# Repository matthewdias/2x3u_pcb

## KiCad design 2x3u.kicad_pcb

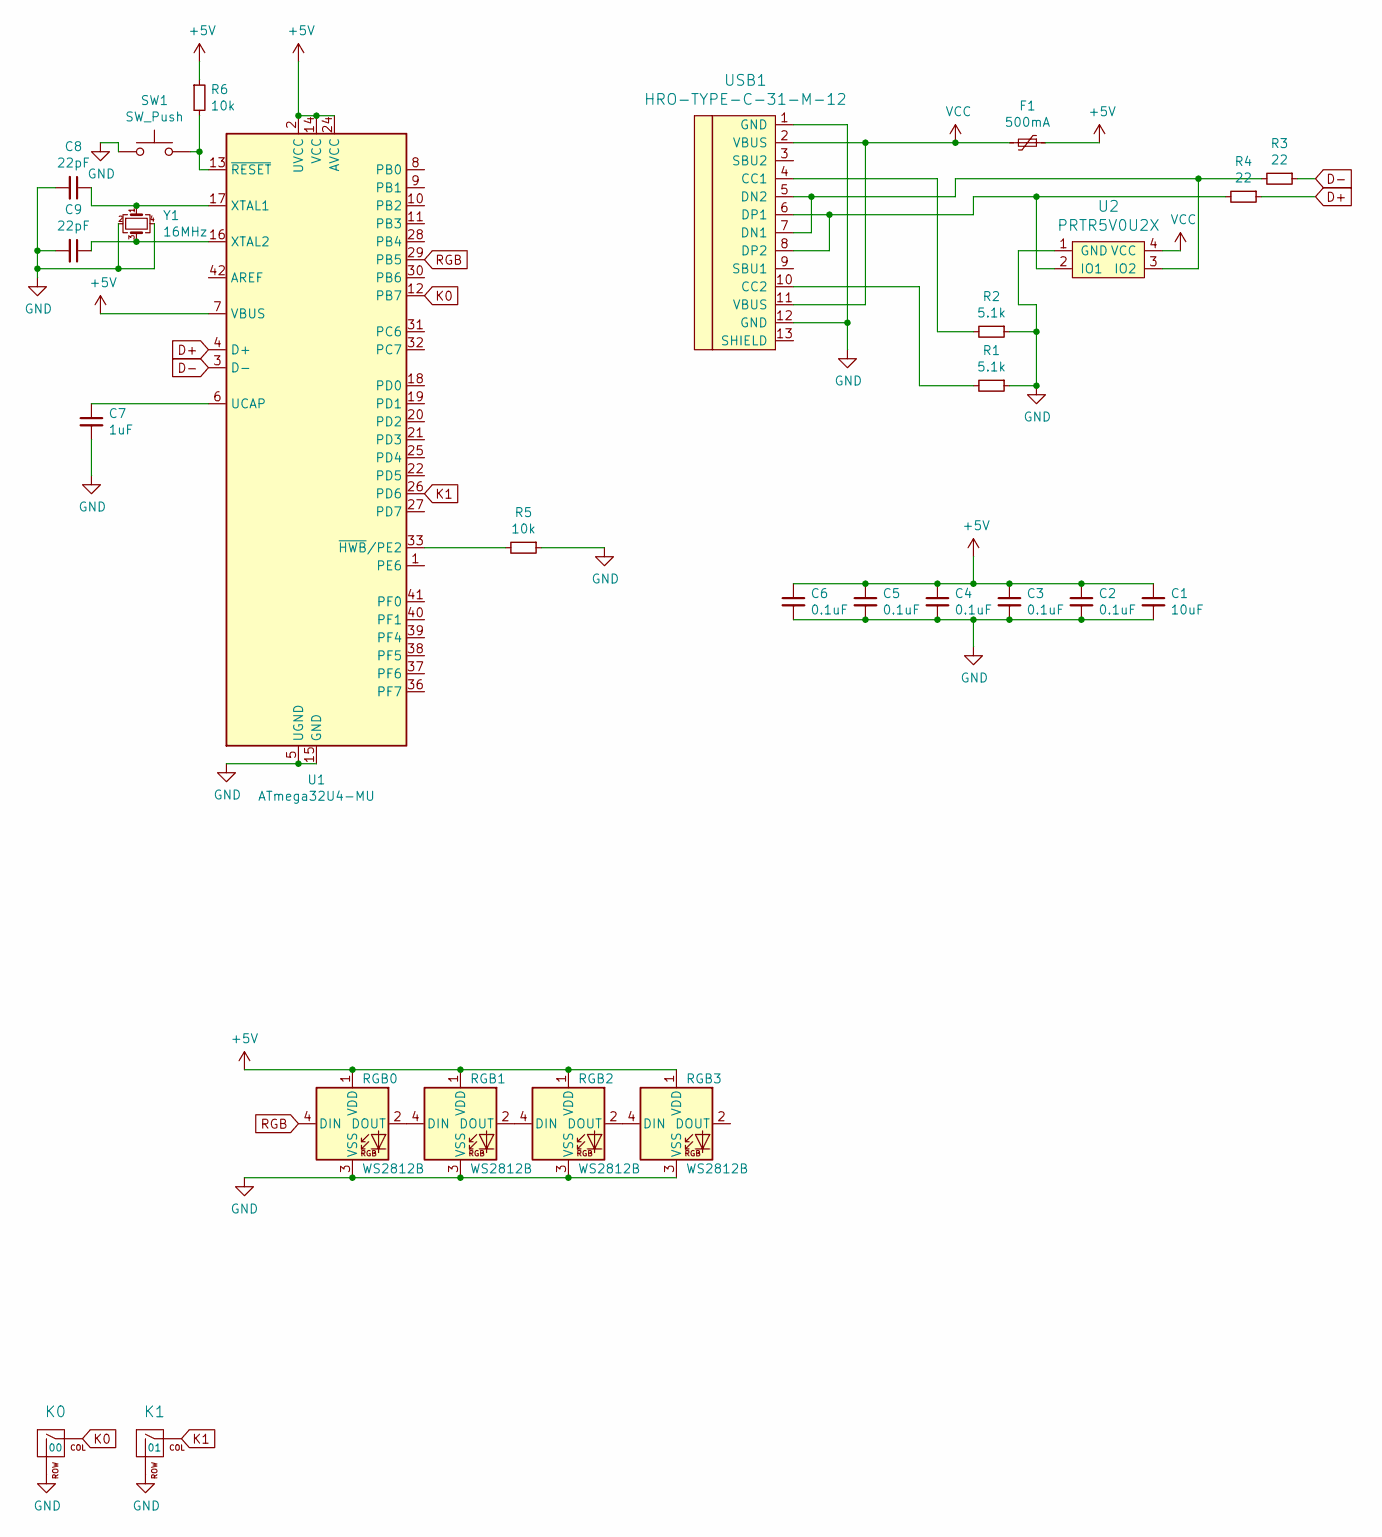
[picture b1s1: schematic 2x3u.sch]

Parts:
C1: 10uF; C_0603_1608Metric
C2, C3, C4, C5, C6: 0.1uF; C_0603_1608Metric
C7: 1uF; C_0603_1608Metric
C8, C9: 22pF; C_0603_1608Metric
F1: 500mA; Fuse_1206_3216Metric
K0, K1: 3U; MXOnly-3U-ReversedStabilizers-NoLED
R1, R2: 5.1k; R_0603_1608Metric
R3, R4: 22; R_0603_1608Metric
R5, R6: 10k; R_0603_1608Metric
RGB0, RGB1, RGB2, RGB3: WS2812B; LED_WS2812B_PLCC4_5.0x5.0mm_P3.2mm
SW1: SW_Push; SKQG-1155865
U1: ATmega32U4-MU; QFN-44-1EP_7x7mm_P0.5mm_EP5.2x5.2mm
U2: PRTR5V0U2X; SOT143B
USB1: HRO-TYPE-C-31-M-12; HRO-TYPE-C-31-M-12-Assembly
Y1: 16MHz; Crystal_SMD_3225-4Pin_3.2x2.5mm

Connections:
+5V: C1.1, C2.1, C3.1, C4.1, C5.1, C6.1, F1.1, R6.1, RGB0.1 (VDD), RGB1.1 (VDD), RGB2.1 (VDD), RGB3.1 (VDD), U1.2 (UVCC), U1.7 (VBUS), U1.14 (VCC), U1.24 (AVCC), U1.34 (VCC), U1.44 (AVCC)
D+: R4.1, U1.4 (D+)
D-: R3.1, U1.3 (D-)
GND: C1.2, C2.2, C3.2, C4.2, C5.2, C6.2, C7.2, C8.2, C9.2, K0.2 (ROW), K1.2 (ROW), R1.1, R2.1, R5.1, RGB0.3 (VSS), RGB1.3 (VSS), RGB2.3 (VSS), RGB3.3 (VSS), SW1.1, U1.5 (UGND), U1.15 (GND), U1.23 (GND), U1.35 (GND), U1.43 (GND), U1.45 (GND), U2.1 (GND), USB1.1 (GND), USB1.12 (GND), Y1.2, Y1.4
K0: K0.1 (COL), U1.12 (PB7)
K1: K1.1 (COL), U1.26 (PD6)
unnamed: C7.1, U1.6 (UCAP)
unnamed: C8.1, U1.17 (XTAL1), Y1.1
unnamed: C9.1, U1.16 (XTAL2), Y1.3
unnamed: R1.2, USB1.10 (CC2)
unnamed: R2.2, USB1.4 (CC1)
unnamed: R3.2, U2.3 (IO2), USB1.5 (DN2), USB1.7 (DN1)
unnamed: R4.2, U2.2 (IO1), USB1.6 (DP1), USB1.8 (DP2)
unnamed: R5.2, U1.33 (~HWB~/PE2)
unnamed: R6.2, SW1.2, U1.13 (~RESET)
unnamed: RGB0.2 (DOUT), RGB1.4 (DIN)
unnamed: RGB1.2 (DOUT), RGB2.4 (DIN)
unnamed: RGB2.2 (DOUT), RGB3.4 (DIN)
RGB: RGB0.4 (DIN), U1.29 (PB5)
VCC: F1.2, U2.4 (VCC), USB1.2 (VBUS), USB1.11 (VBUS)

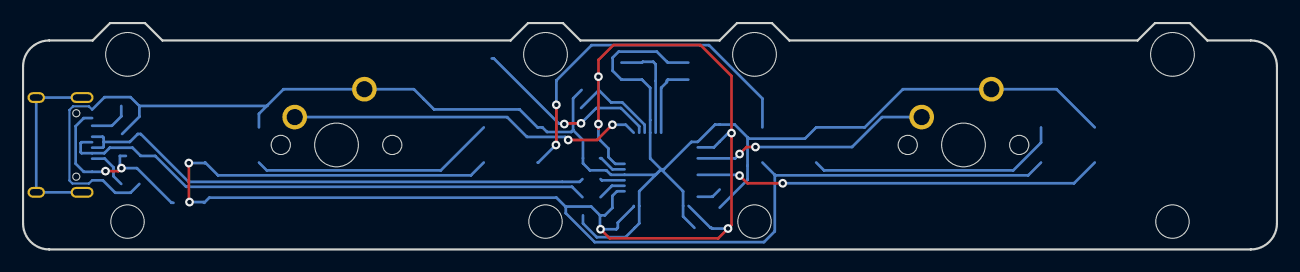
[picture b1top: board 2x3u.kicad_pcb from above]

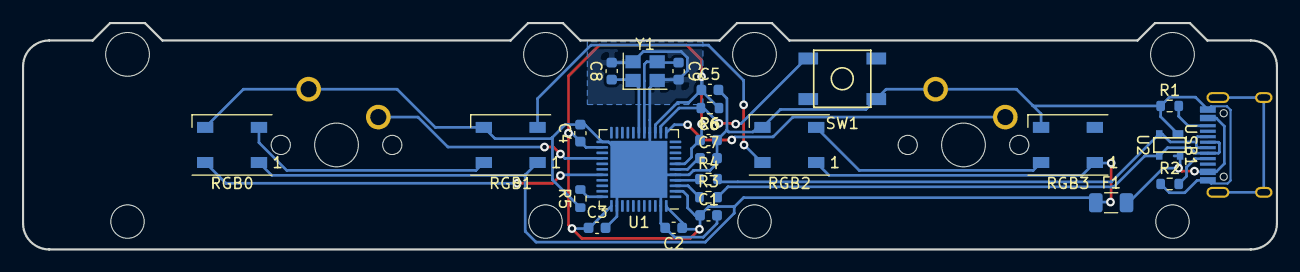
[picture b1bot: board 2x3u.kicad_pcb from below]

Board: 2 copper layers, 114.3 x 20.6 mm, 27 parts (25 on the bottom side), 20 nets.
